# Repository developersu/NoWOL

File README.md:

# NoWOL

Open initiative to rule PC power supply over the net.

Узнай о чём речь здесь https://developersu.blogspot.com/2018/04/nowol-1.html

## Requirements

* Eagle CAD 7.7 (sci-electronics/eagle)

* dev-embedded/arduino

* Android 4.0 + [see android project](https://github.com/developersu/NoWOL-APK) or WEB-browser

*  Arduino nano (but not important)

  OR 

  Part     Value          Device         Package       Library       Sheet

C1       22pF           C-EUC0603      C0603         resistor      1

C2       22pF           C-EUC0603      C0603         resistor      1

C3       10uF           CC0603         C0603         eagle-ltspice 1

C4       22uF           CC0603         C0603         eagle-ltspice 1

IC1      MEGA328p       MEGA328p       TQFP32-08     avr-6         1

IC3      LM1117IMPX-3.3 LM1117IMPX-3.3 SOT223        lm1117        1

JP1                     PINHD-2X5      2X05          pinhead       1

JP3                     PINHD-1X2      1X02          pinhead       1

Q1       16MHz          XTAL/S         QS            special       1

SV1                     MA05-1         MA05-1        con-lstb      1

U1                      USB""          USB-MICRO-SMD MicroUSB      1

AND

КР293КП4А                           x2

PINHD-1X6                           x2

Resistor 450 Ω OR 470 Ω (0204/5)    x2

Resistor 330 Ω (0204/5)             x1

PINHD-1X5                           x1

## License

Source code and hardware-related documents (such as Eagle PCB layout) spreads under the GNU General Public License v.3. You can find it in LICENSE file. 

PAY ATTENTION ON EXCEPTIONS!

All rights to КР293КП4А.pdf datasheet file belongs to 'ЗАО ПРОТОН', г.Орёл, Россия.

No idea who owns eagle_files/lib, but they're NOT mine. Please let me know if you're owner and want me to remove them/update information regarding authorship.

Library ethercard-master (arduino_sketchbook/libraries/ethercard-master/) spreads under GNU GPL2. 

Information about author and more see in arduino_sketchbook/libraries/ethercard-master/README.md file.

Images, if not noted, spreads under a Creative Commons Attribution 4.0 International License. Please see http://creativecommons.org/licenses/by/4.0/ to know more.

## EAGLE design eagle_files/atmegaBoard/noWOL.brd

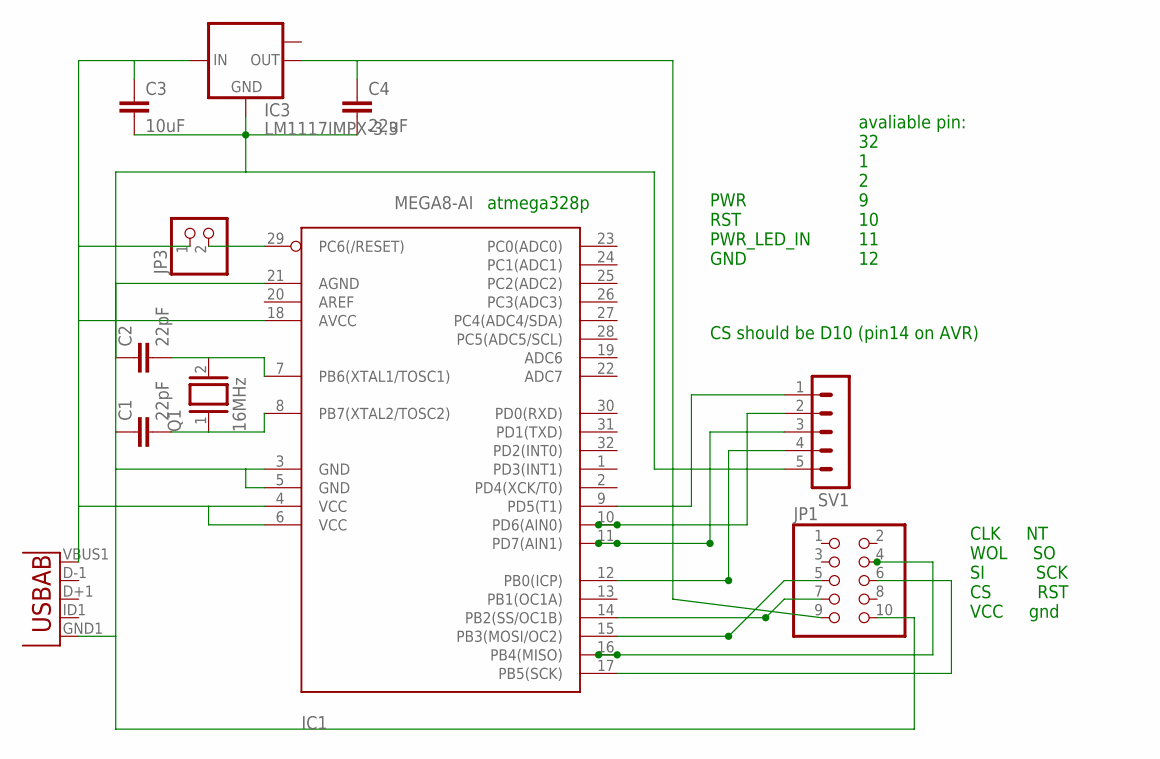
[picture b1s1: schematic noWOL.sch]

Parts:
C1, C2: 22pF; C0603
C3: 10uF; C0603
C4: 22uF; C0603
IC1: MEGA8-AI; TQFP32-08
IC3: LM1117IMPX-3.3; SOT223
JP1: PINHD-2X5; 2X05
JP3: PINHD-1X2; 1X02
Q1: 16MHz; QS
SV1: MA05-1
U1: USB""; USB-MICRO-SMD

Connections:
unnamed: C2.2, IC1.7 (PB6(XTAL1/TOSC1)), Q1.2
unnamed: C1.2, IC1.8 (PB7(XTAL2/TOSC2)), Q1.1
unnamed: IC1.29 (PC6(/RESET)), JP3.2
unnamed: C3.1, IC1.4 (VCC), IC1.6 (VCC), IC1.18 (AVCC), IC3.3 (IN), JP3.1, U1.VBUS1 (VBUS)
unnamed: IC1.16 (PB4(MISO)), JP1.4
unnamed: IC1.15 (PB3(MOSI/OC2)), JP1.5
unnamed: IC1.14 (PB2(SS/OC1B)), JP1.7
unnamed: IC1.17 (PB5(SCK)), JP1.6
unnamed: IC1.10 (PD6(AIN0)), SV1.2
unnamed: IC1.11 (PD7(AIN1)), SV1.3
unnamed: IC1.12 (PB0(ICP)), SV1.4
unnamed: IC1.9 (PD5(T1)), SV1.1
unnamed: C4.1, IC3.2 (OUT), JP1.9
unnamed: C1.1, C2.1, C3.2, C4.2, IC1.3 (GND), IC1.5 (GND), IC1.21 (AGND), IC3.1 (GND), JP1.10, SV1.5, U1.GND1 (GND)

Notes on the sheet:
PWR RST PWR_LED_IN GND
CLK NT WOL SO SI SCK CS RST VCC gnd
CS should be D10 (pin14 on AVR)
avaliable pin: 32 1 2 9 10 11 12
atmega328p

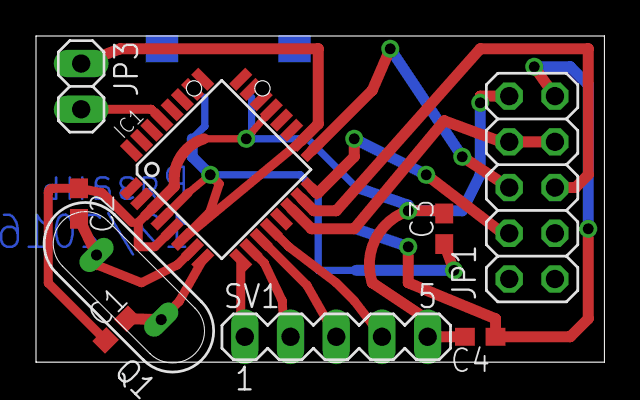
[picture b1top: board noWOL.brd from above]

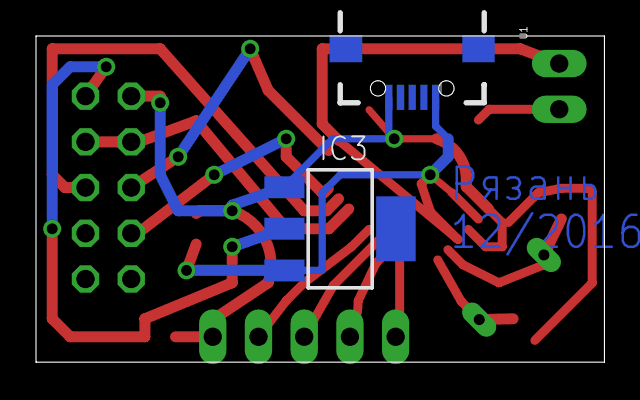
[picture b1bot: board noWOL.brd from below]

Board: 2 copper layers, 31.6 x 18.1 mm, 11 parts (2 on the bottom side), 14 nets.

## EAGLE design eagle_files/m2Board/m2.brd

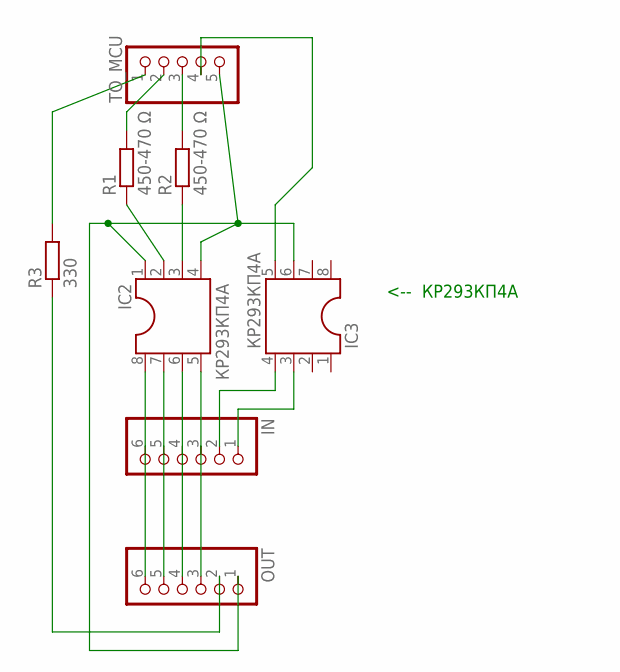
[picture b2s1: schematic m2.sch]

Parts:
IC2, IC3: КР293КП4А; DIL08
IN: PINHD-1X6; 1X06
OUT: PINHD-1X6; 1X06
R1, R2: 450-470 Ω; 0204/5
R3: 330; 0204/5
TO_MCU: PINHD-1X5; 1X05

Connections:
unnamed: IC2.8, IN.6, OUT.6
unnamed: IC2.2, R1.1
unnamed: IC2.3, R2.1
unnamed: IC2.7, IN.5, OUT.5
unnamed: IC2.1, IC2.4, IC3.6, OUT.1, TO_MCU.5
unnamed: IC2.6, IN.4, OUT.4
unnamed: IC2.5, IN.3, OUT.3
unnamed: IC3.4, IN.2
unnamed: IC3.3, IN.1
unnamed: OUT.2, R3.1
unnamed: R1.2, TO_MCU.2
unnamed: R2.2, TO_MCU.3
unnamed: IC3.5, TO_MCU.4
unnamed: R3.2, TO_MCU.1

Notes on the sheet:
<-- КР293КП4А

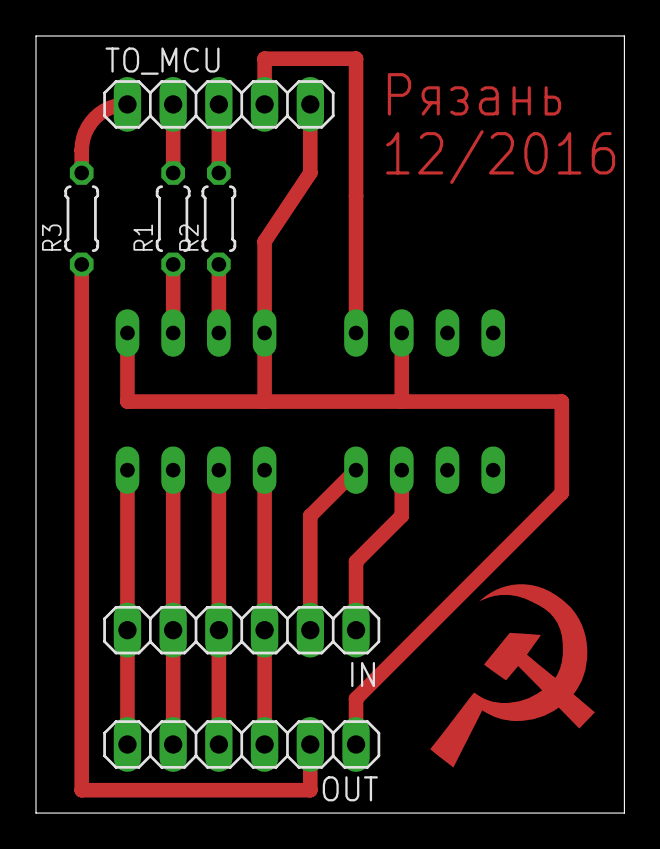
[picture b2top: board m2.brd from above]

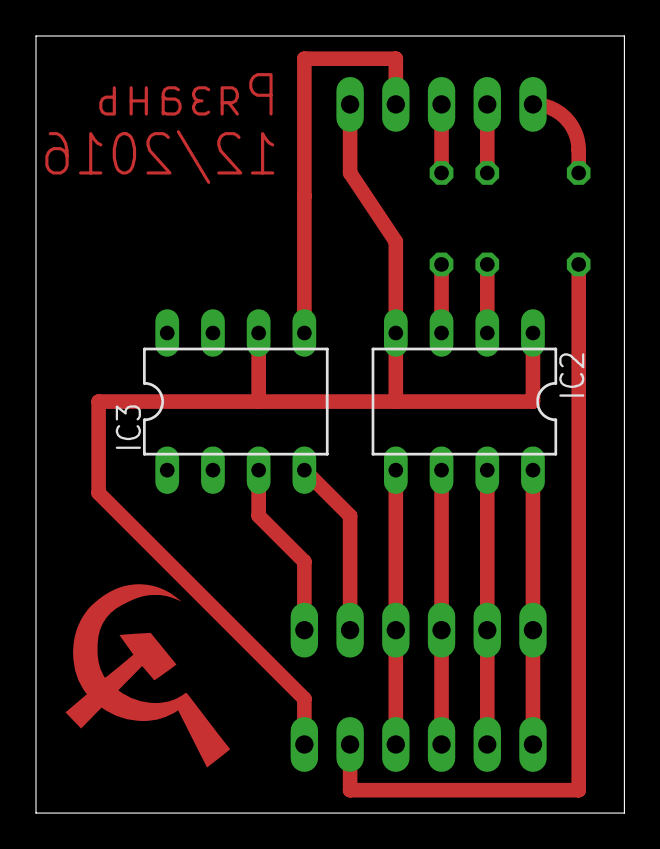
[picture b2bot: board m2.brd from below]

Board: 2 copper layers, 32.7 x 43.2 mm, 8 parts (2 on the bottom side), 14 nets.

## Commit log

2018-04-10 release
2018-04-10 rm tmp files
2019-08-02 readme update
